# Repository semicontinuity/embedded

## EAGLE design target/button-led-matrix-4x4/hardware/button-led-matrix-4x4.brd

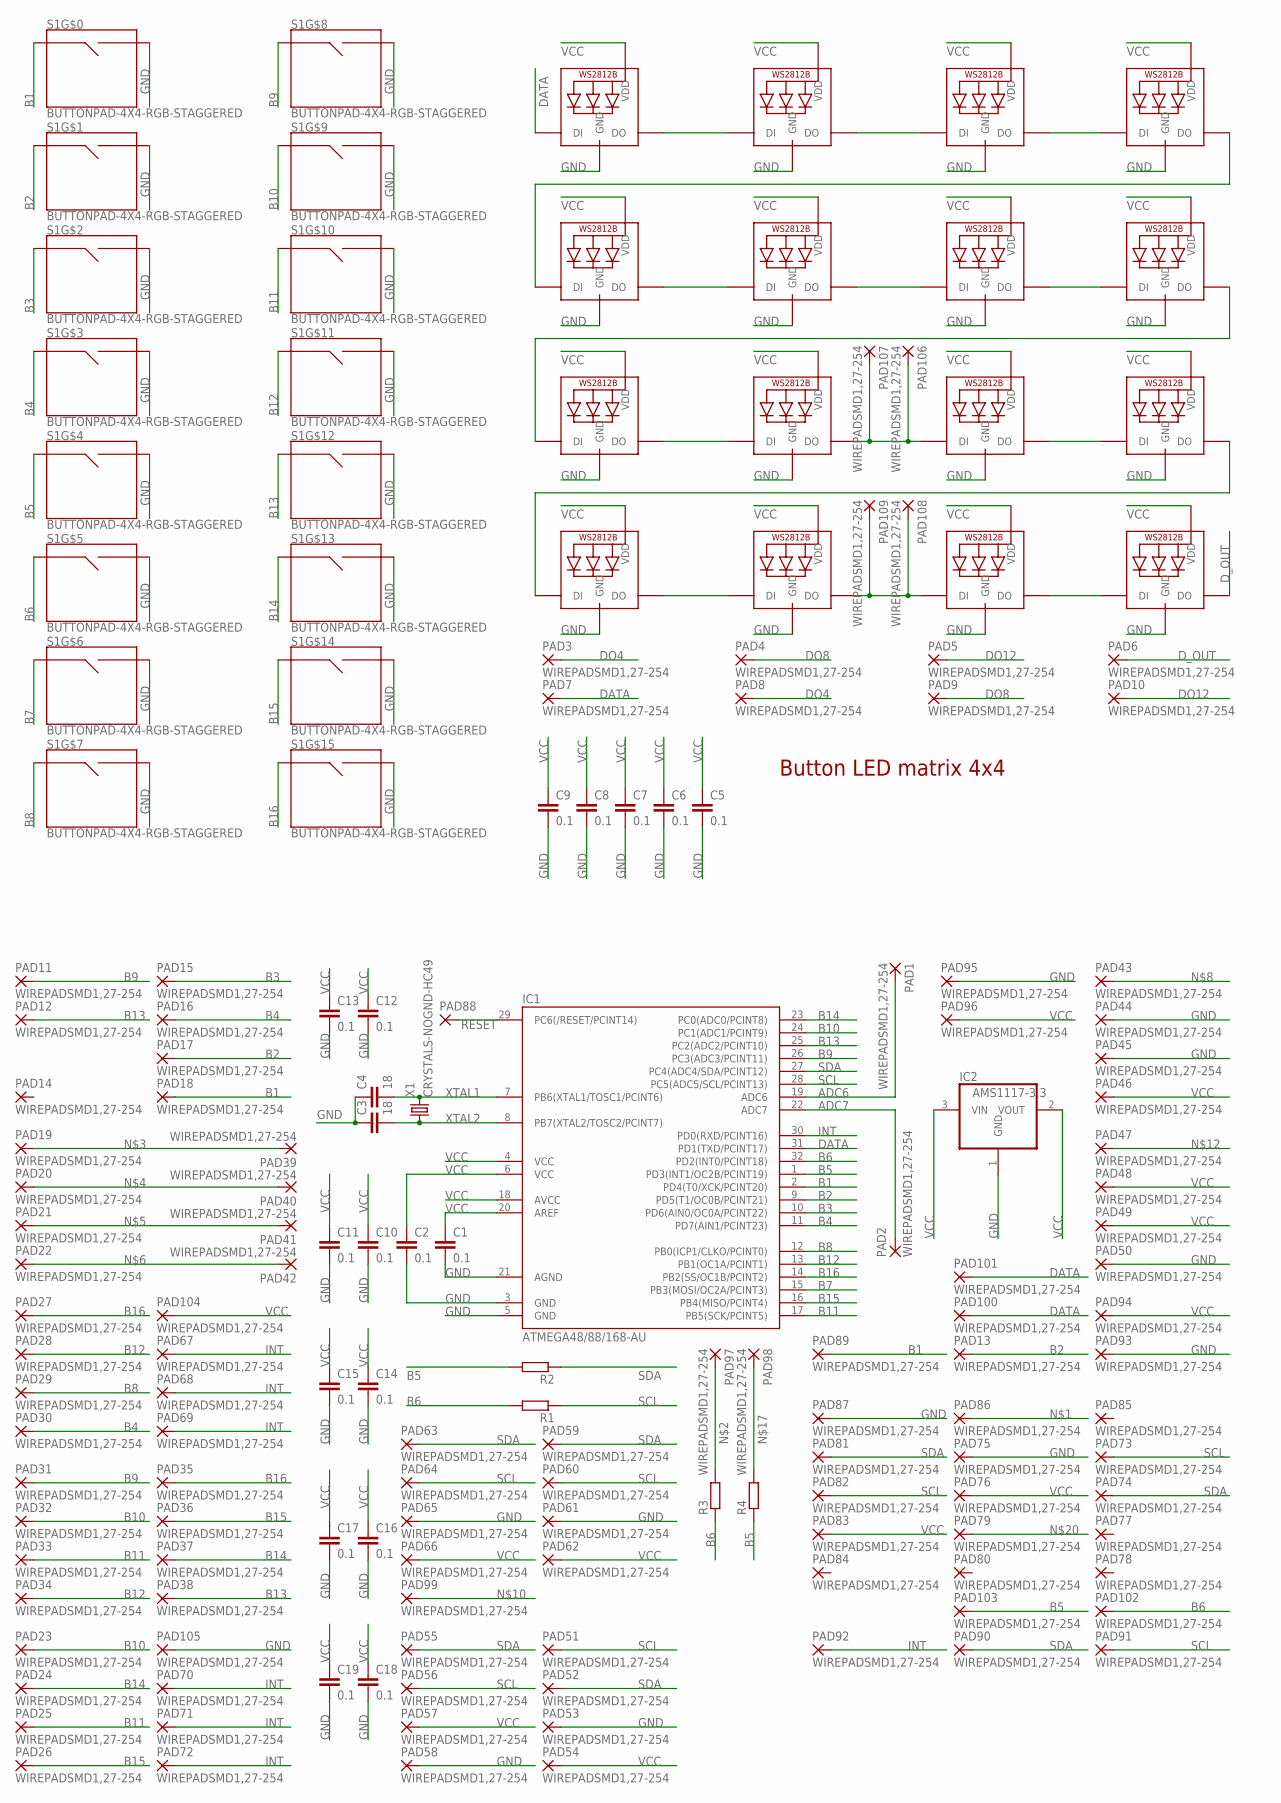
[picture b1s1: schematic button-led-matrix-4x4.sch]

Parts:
C1, C2, C5, C6, C7, C8, C9, C10, C11, C12, C13, C14, C15, C16, C17, C18, C19: 0.1; C0805
C3, C4: 18; C0805
IC1: ATMEGA48/88/168-AU; TQFP32-08
IC2: AMS1117-3.3; SOT223
LED1, LED2, LED3, LED4, LED5, LED6, LED7, LED8, LED9, LED10, LED11, LED12, LED13, LED14, LED15, LED16: WS2812B_5050N; WS2812B-NARROW
PAD1, PAD2, PAD3, PAD4, PAD5, PAD6, PAD7, PAD8, PAD9, PAD10, PAD11, PAD12, PAD13, PAD14, PAD15, PAD16, PAD17, PAD18, PAD19, PAD20, PAD21, PAD22, PAD23, PAD24, PAD25, PAD26, PAD27, PAD28, PAD29, PAD30, PAD31, PAD32, PAD33, PAD34, PAD35, PAD36, PAD37, PAD38, PAD39, PAD40, PAD41, PAD42, PAD43, PAD44, PAD45, PAD46, PAD47, PAD48, PAD49, PAD50, PAD51, PAD52, PAD53, PAD54, PAD55, PAD56, PAD57, PAD58, PAD59, PAD60, PAD61, PAD62, PAD63, PAD64, PAD65, PAD66, PAD67, PAD68, PAD69, PAD70, PAD71, PAD72, PAD73, PAD74, PAD75, PAD76, PAD77, PAD78, PAD79, PAD80, PAD81, PAD82, PAD83, PAD84, PAD85, PAD86, PAD87, PAD89, PAD90, PAD91, PAD92, PAD93, PAD94, PAD95, PAD96, PAD97, PAD98, PAD99, PAD100, PAD101, PAD102, PAD103, PAD104, PAD105, PAD106, PAD107, PAD108, PAD109: WIREPADSMD1,27-254; SMD1,27-2,54
PAD88: 1,6/0,8
R1, R2: R-EU_R1206; R1206
R3, R4: R-EU_R0805; R0805
S1: BUTTONPAD-4X4-RGB-STAGGERED; BUTTONPAD-4X4-STAGGERED
X1: CRYSTALS-NOGND-HC49; HC49

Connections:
ADC6: IC1.19 (ADC6), PAD1.1
ADC7: IC1.22 (ADC7), PAD2.1
B1: IC1.2 (PD4(T0/XCK/PCINT20)), PAD18.1, PAD89.1, S1.SIG0 (SIG1)
B2: IC1.9 (PD5(T1/OC0B/PCINT21)), PAD13.1, PAD17.1, S1.SIG2 (SIG1)
B3: IC1.10 (PD6(AIN0/OC0A/PCINT22)), PAD15.1, S1.SIG4 (SIG1)
B4: IC1.11 (PD7(AIN1/PCINT23)), PAD16.1, PAD30.1, S1.SIG6 (SIG1)
B5: IC1.1 (PD3(INT1/OC2B/PCINT19)), PAD103.1, R2.2, R4.1, S1.SIG8 (SIG1)
B6: IC1.32 (PD2(INT0/PCINT18)), PAD102.1, R1.2, R3.1, S1.SIG10 (SIG1)
B7: IC1.15 (PB3(MOSI/OC2A/PCINT3)), S1.SIG12 (SIG1)
B8: IC1.12 (PB0(ICP1/CLKO/PCINT0)), PAD29.1, S1.SIG14 (SIG1)
B9: IC1.26 (PC3(ADC3/PCINT11)), PAD11.1, PAD31.1, S1.SIG16 (SIG1)
B10: IC1.24 (PC1(ADC1/PCINT9)), PAD23.1, PAD32.1, S1.SIG18 (SIG1)
B11: IC1.17 (PB5(SCK/PCINT5)), PAD25.1, PAD33.1, S1.SIG20 (SIG1)
B12: IC1.13 (PB1(OC1A/PCINT1)), PAD28.1, PAD34.1, S1.SIG22 (SIG1)
B13: IC1.25 (PC2(ADC2/PCINT10)), PAD12.1, PAD38.1, S1.SIG24 (SIG1)
B14: IC1.23 (PC0(ADC0/PCINT8)), PAD24.1, PAD37.1, S1.SIG26 (SIG1)
B15: IC1.16 (PB4(MISO/PCINT4)), PAD26.1, PAD36.1, S1.SIG28 (SIG1)
B16: IC1.14 (PB2(SS/OC1B/PCINT2)), PAD27.1, PAD35.1, S1.SIG30 (SIG1)
DATA: IC1.31 (PD1(TXD/PCINT17)), LED1.4-DIN (DI), PAD7.1, PAD100.1, PAD101.1
DO1: LED1.2-DOUT (DO), LED2.4-DIN (DI)
DO2: LED2.2-DOUT (DO), LED3.4-DIN (DI)
DO3: LED3.2-DOUT (DO), LED4.4-DIN (DI)
DO4: LED4.2-DOUT (DO), LED5.4-DIN (DI), PAD3.1, PAD8.1
DO6: LED6.2-DOUT (DO), LED7.4-DIN (DI)
DO7: LED7.2-DOUT (DO), LED8.4-DIN (DI)
DO8: LED8.2-DOUT (DO), LED9.4-DIN (DI), PAD4.1, PAD9.1
DO9: LED9.2-DOUT (DO), LED10.4-DIN (DI)
DO10: LED10.2-DOUT (DO), LED11.4-DIN (DI), PAD106.1, PAD107.1
DO11: LED11.2-DOUT (DO), LED12.4-DIN (DI)
DO12: LED12.2-DOUT (DO), LED13.4-DIN (DI), PAD5.1, PAD10.1
DO13: LED13.2-DOUT (DO), LED14.4-DIN (DI)
DO14: LED14.2-DOUT (DO), LED15.4-DIN (DI), PAD108.1, PAD109.1
DO15: LED15.2-DOUT (DO), LED16.4-DIN (DI)
D_OUT: LED16.2-DOUT (DO), PAD6.1
FO5: LED5.2-DOUT (DO), LED6.4-DIN (DI)
GND: C1.2, C2.2, C3.1, C4.1, C5.2, C6.2, C7.2, C8.2, C9.2, C10.2, C11.2, C12.2, C13.2, C14.2, C15.2, C16.2, C17.2, C18.2, C19.2, IC1.3 (GND), IC1.5 (GND), IC1.21 (AGND), IC2.1 (GND), LED1.3-GND (GND), LED2.3-GND (GND), LED3.3-GND (GND), LED4.3-GND (GND), LED5.3-GND (GND), LED6.3-GND (GND), LED7.3-GND (GND), LED8.3-GND (GND), LED9.3-GND (GND), LED10.3-GND (GND), LED11.3-GND (GND), LED12.3-GND (GND), LED13.3-GND (GND), LED14.3-GND (GND), LED15.3-GND (GND), LED16.3-GND (GND), PAD44.1, PAD45.1, PAD50.1, PAD53.1, PAD58.1, PAD61.1, PAD65.1, PAD75.1, PAD87.1, PAD93.1, PAD95.1, PAD105.1, S1.SIG1 (SIG2), S1.SIG3 (SIG2), S1.SIG5 (SIG2), S1.SIG7 (SIG2), S1.SIG9 (SIG2), S1.SIG11 (SIG2), S1.SIG13 (SIG2), S1.SIG15 (SIG2), S1.SIG17 (SIG2), S1.SIG19 (SIG2), S1.SIG21 (SIG2), S1.SIG23 (SIG2), S1.SIG25 (SIG2), S1.SIG27 (SIG2), S1.SIG29 (SIG2), S1.SIG31 (SIG2)
INT: IC1.30 (PD0(RXD/PCINT16)), PAD67.1, PAD68.1, PAD69.1, PAD70.1, PAD71.1, PAD72.1, PAD92.1
unnamed: PAD97.1, R3.2
unnamed: PAD19.1, PAD39.1
unnamed: PAD20.1, PAD40.1
unnamed: PAD21.1, PAD41.1
unnamed: PAD22.1, PAD42.1
unnamed: PAD98.1, R4.2
RESET: IC1.29 (PC6(/RESET/PCINT14)), PAD88.1
SCL: IC1.28 (PC5(ADC5/SCL/PCINT13)), PAD51.1, PAD56.1, PAD60.1, PAD64.1, PAD73.1, PAD82.1, PAD91.1, R1.1
SDA: IC1.27 (PC4(ADC4/SDA/PCINT12)), PAD52.1, PAD55.1, PAD59.1, PAD63.1, PAD74.1, PAD81.1, PAD90.1, R2.1
VCC: C1.1, C2.1, C5.1, C6.1, C7.1, C8.1, C9.1, C10.1, C11.1, C12.1, C13.1, C14.1, C15.1, C16.1, C17.1, C18.1, C19.1, IC1.4 (VCC), IC1.6 (VCC), IC1.18 (AVCC), IC1.20 (AREF), IC2.2 (VOUT), IC2.3 (VIN), LED1.1-VDD (VDD), LED2.1-VDD (VDD), LED3.1-VDD (VDD), LED4.1-VDD (VDD), LED5.1-VDD (VDD), LED6.1-VDD (VDD), LED7.1-VDD (VDD), LED8.1-VDD (VDD), LED9.1-VDD (VDD), LED10.1-VDD (VDD), LED11.1-VDD (VDD), LED12.1-VDD (VDD), LED13.1-VDD (VDD), LED14.1-VDD (VDD), LED15.1-VDD (VDD), LED16.1-VDD (VDD), PAD46.1, PAD48.1, PAD49.1, PAD54.1, PAD57.1, PAD62.1, PAD66.1, PAD76.1, PAD83.1, PAD94.1, PAD96.1, PAD104.1
XTAL1: C4.2, IC1.7 (PB6(XTAL1/TOSC1/PCINT6)), X1.2
XTAL2: C3.2, IC1.8 (PB7(XTAL2/TOSC2/PCINT7)), X1.1

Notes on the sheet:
Button LED matrix 4x4

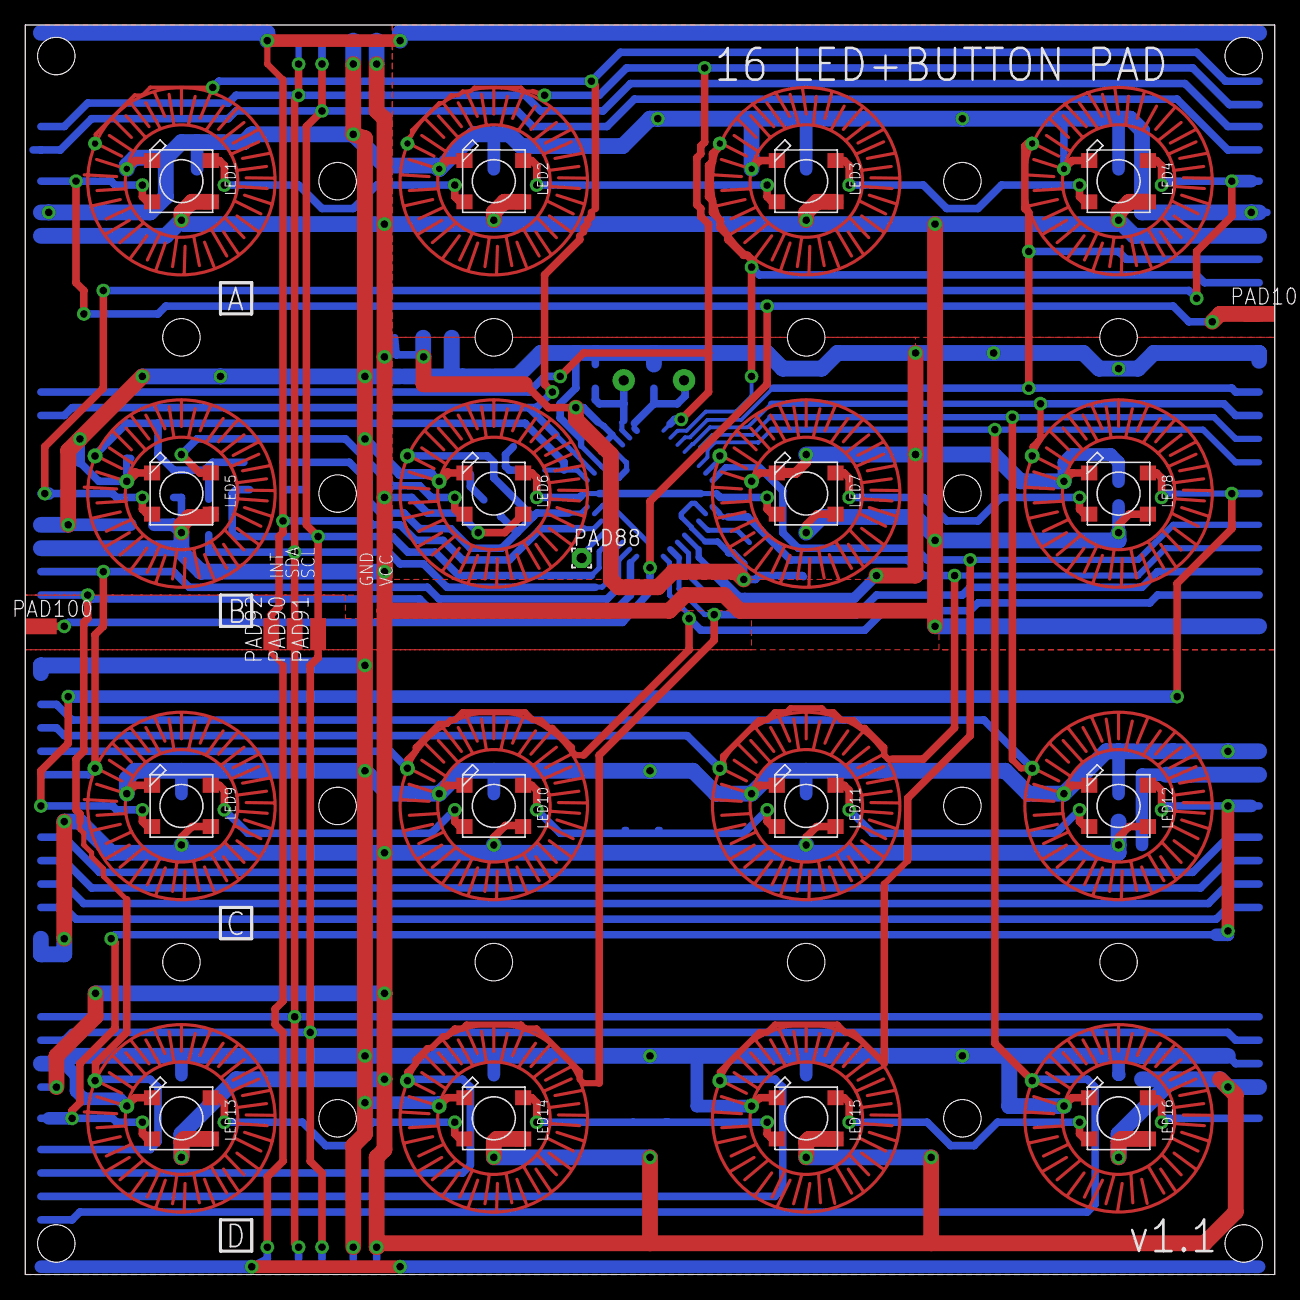
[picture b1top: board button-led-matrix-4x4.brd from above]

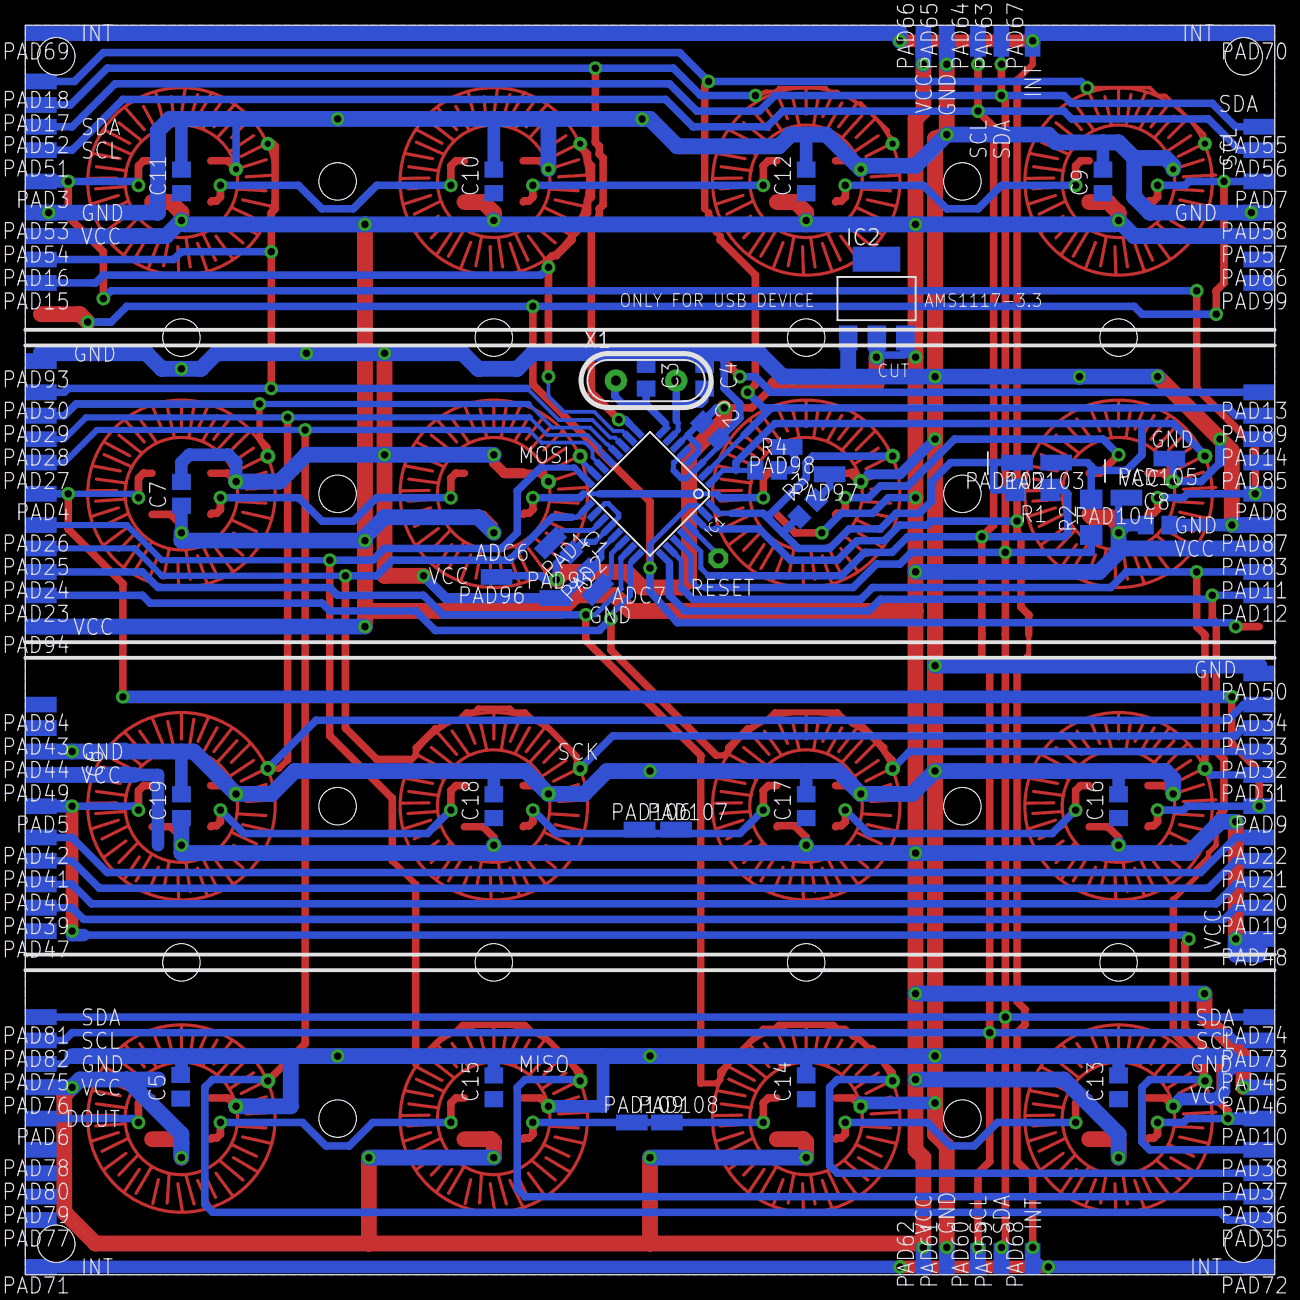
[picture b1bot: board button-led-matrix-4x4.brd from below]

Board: 2 copper layers, 100.0 x 100.0 mm, 152 parts (129 on the bottom side), 49 nets.

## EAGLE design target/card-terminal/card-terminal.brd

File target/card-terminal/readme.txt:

Card terminal

Device in development, featuring smartcard or SIM card slot, SPI interface, LCD display, keypad, serial and USB port.

Possible uses:

* CCID-compliant USB card terminal fith keypad and display
* USB HID device
* USB CDC device (USB-to-serial)
* Application host - providing resources to application running on a AVR card (Funcard)
* USB-to-SPI converter
* AVR programmer
* Generic development board

For serial connector, it is possible to use 6-pin or 4-pin FireWire connectors
(small size, hard to attach wrong cable, right number of pins,
crossed pairs in the cable - good for crossing RX/TX, RTS/CTS)

Revision A board is designed for AT90USB162 and SIM card slot.
Due to a small number of pins, peripherals are multiplexed and some glue logic is required.

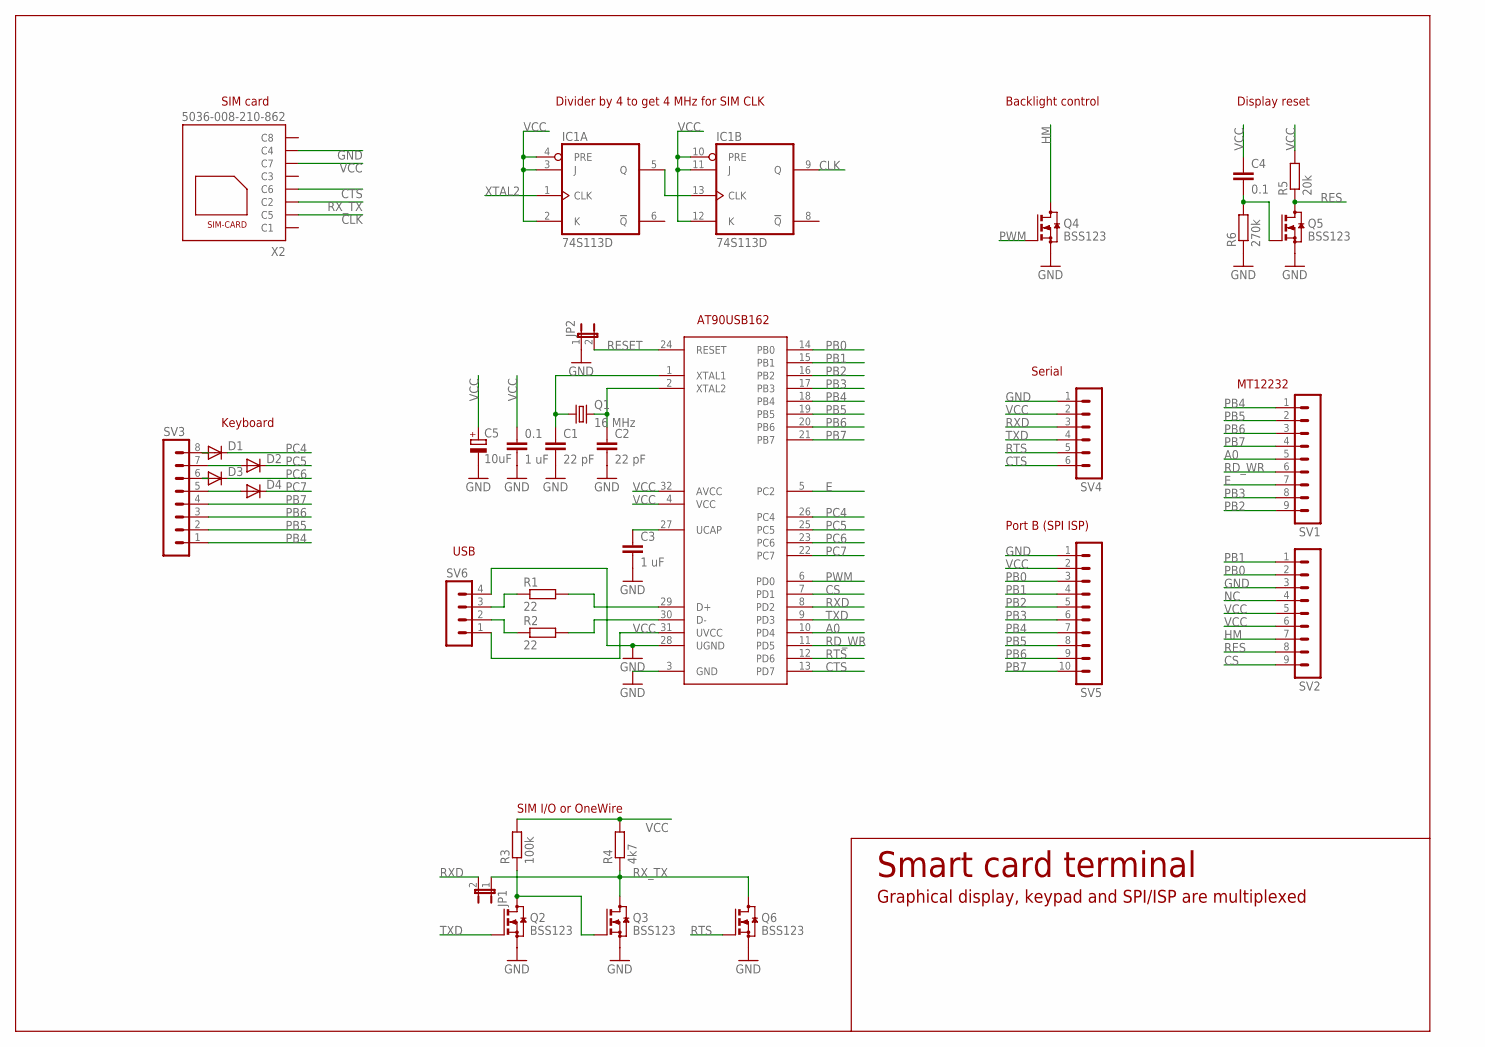
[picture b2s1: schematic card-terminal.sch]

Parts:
0.1: 1 uF; C0805
C1, C2: 22 pF; C0805
C3: 1 uF; C0805
C4: 0.1; C0805
C5: 10uF; 153CLV-0505
D1, D2, D3, D4: DIODE-MINIMELF; MINIMELF
IC1: 74S113D; SO14
JP1, JP2: JP1E; JP1
Q1: 16 MHz; HC49/S
Q2, Q3, Q4, Q5, Q6: BSS123; SOT23
R1, R2: 22; M0805
R3: 100k; M0805
R4: 4k7; M0805
R5: 20k; M0805
R6: 270k; M0805
SV1, SV2: MA09-1W
SV3: MA08-1
SV4: MA06-1
SV5: MA10-1W
SV6: MA04-1
U$1: AT90USB162; VQFP32
X2: 5036-008-210-862; 5036_008_210_862

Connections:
A0: SV1.5, U$1.10 (PD4)
CLK: IC1.9 (Q), X2.C5
CS: SV2.9, U$1.7 (PD1)
CTS: SV4.6, U$1.13 (PD7), X2.C6
E: SV1.7, U$1.5 (PC2)
F2: IC1.5 (Q), IC1.13 (CLK)
GND: 0.1.2, C1.2, C2.2, C3.2, C5.-, IC1.7 (GND), JP2.1, Q2.2 (S), Q3.2 (S), Q4.2 (S), Q5.2 (S), Q6.2 (S), R6.1, SV2.3, SV4.1, SV5.1, SV6.4, U$1.3 (GND), U$1.28 (UGND), X2.C4
HM: Q4.3 (D), SV2.7
unnamed: D1.A, SV3.8
unnamed: D2.A, SV3.7
unnamed: C4.2, Q5.1 (G), R6.2
unnamed: D3.A, SV3.6
unnamed: D4.A, SV3.5
unnamed: Q2.3 (D), Q3.1 (G), R3.1
unnamed: C3.1, U$1.27 (UCAP)
unnamed: R2.2, U$1.30 (D-)
unnamed: R1.2, U$1.29 (D+)
unnamed: R1.1, SV6.3
unnamed: R2.1, SV6.2
NC: SV2.4
PB0: SV2.2, SV5.3, U$1.14 (PB0)
PB1: SV2.1, SV5.4, U$1.15 (PB1)
PB2: SV1.9, SV5.5, U$1.16 (PB2)
PB3: SV1.8, SV5.6, U$1.17 (PB3)
PB4: SV1.1, SV3.1, SV5.7, U$1.18 (PB4)
PB5: SV1.2, SV3.2, SV5.8, U$1.19 (PB5)
PB6: SV1.3, SV3.3, SV5.9, U$1.20 (PB6)
PB7: SV1.4, SV3.4, SV5.10, U$1.21 (PB7)
PC4: D1.C, U$1.26 (PC4)
PC5: D2.C, U$1.25 (PC5)
PC6: D3.C, U$1.23 (PC6)
PC7: D4.C, U$1.22 (PC7)
PWM: Q4.1 (G), U$1.6 (PD0)
RD_WR: SV1.6, U$1.11 (PD5)
RES: Q5.3 (D), R5.1, SV2.8
RESET: JP2.2, U$1.24 (RESET)
RTS: Q6.1 (G), SV4.5, U$1.12 (PD6)
RXD: JP1.2, SV4.3, U$1.8 (PD2)
RX_TX: JP1.1, Q3.3 (D), Q6.3 (D), R4.1, X2.C2
TXD: Q2.1 (G), SV4.4, U$1.9 (PD3)
VCC: 0.1.1, C4.1, C5.+, IC1.2 (K), IC1.3 (J), IC1.4 (PRE), IC1.10 (PRE), IC1.11 (J), IC1.12 (K), IC1.14 (VCC), R3.2, R4.2, R5.2, SV2.5, SV2.6, SV4.2, SV5.2, SV6.1, U$1.4 (VCC), U$1.31 (UVCC), U$1.32 (AVCC), X2.C7
XTAL1: C1.1, Q1.1, U$1.1 (XTAL1)
XTAL2: C2.1, IC1.1 (CLK), Q1.2, U$1.2 (XTAL2)

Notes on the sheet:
Keyboard
SIM card
SIM I/O or OneWire
Backlight control
Display reset
USB
AT90USB162
Divider by 4 to get 4 MHz for SIM CLK
MT12232
Serial
Port B (SPI ISP)
Smart card terminal
Graphical display, keypad and SPI/ISP are multiplexed

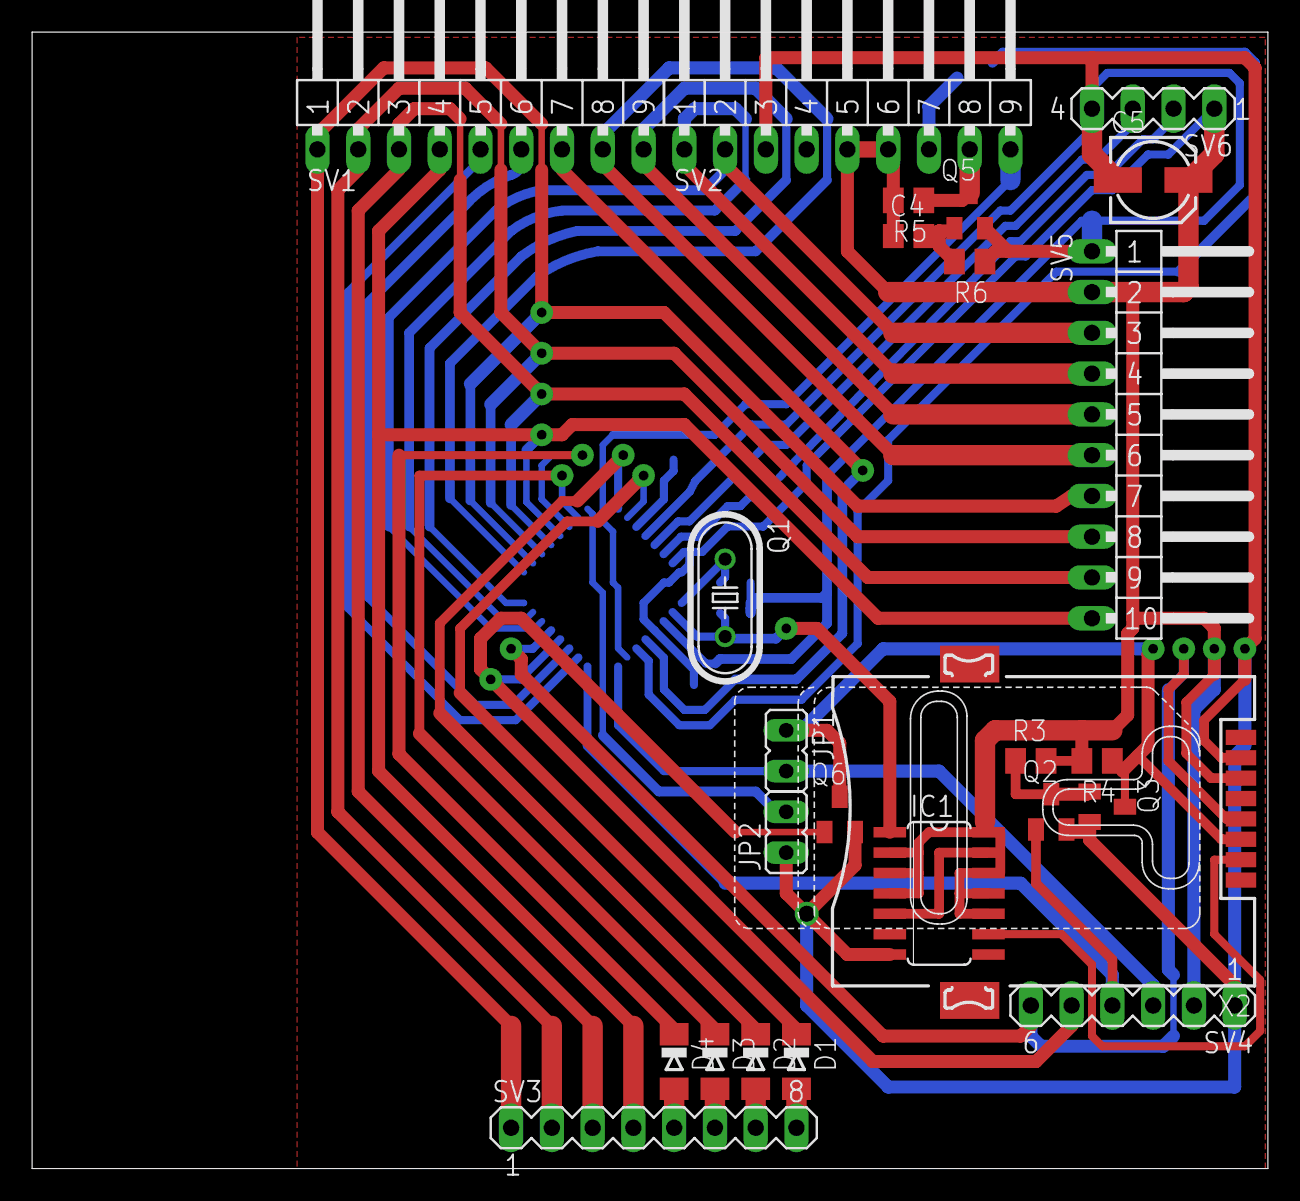
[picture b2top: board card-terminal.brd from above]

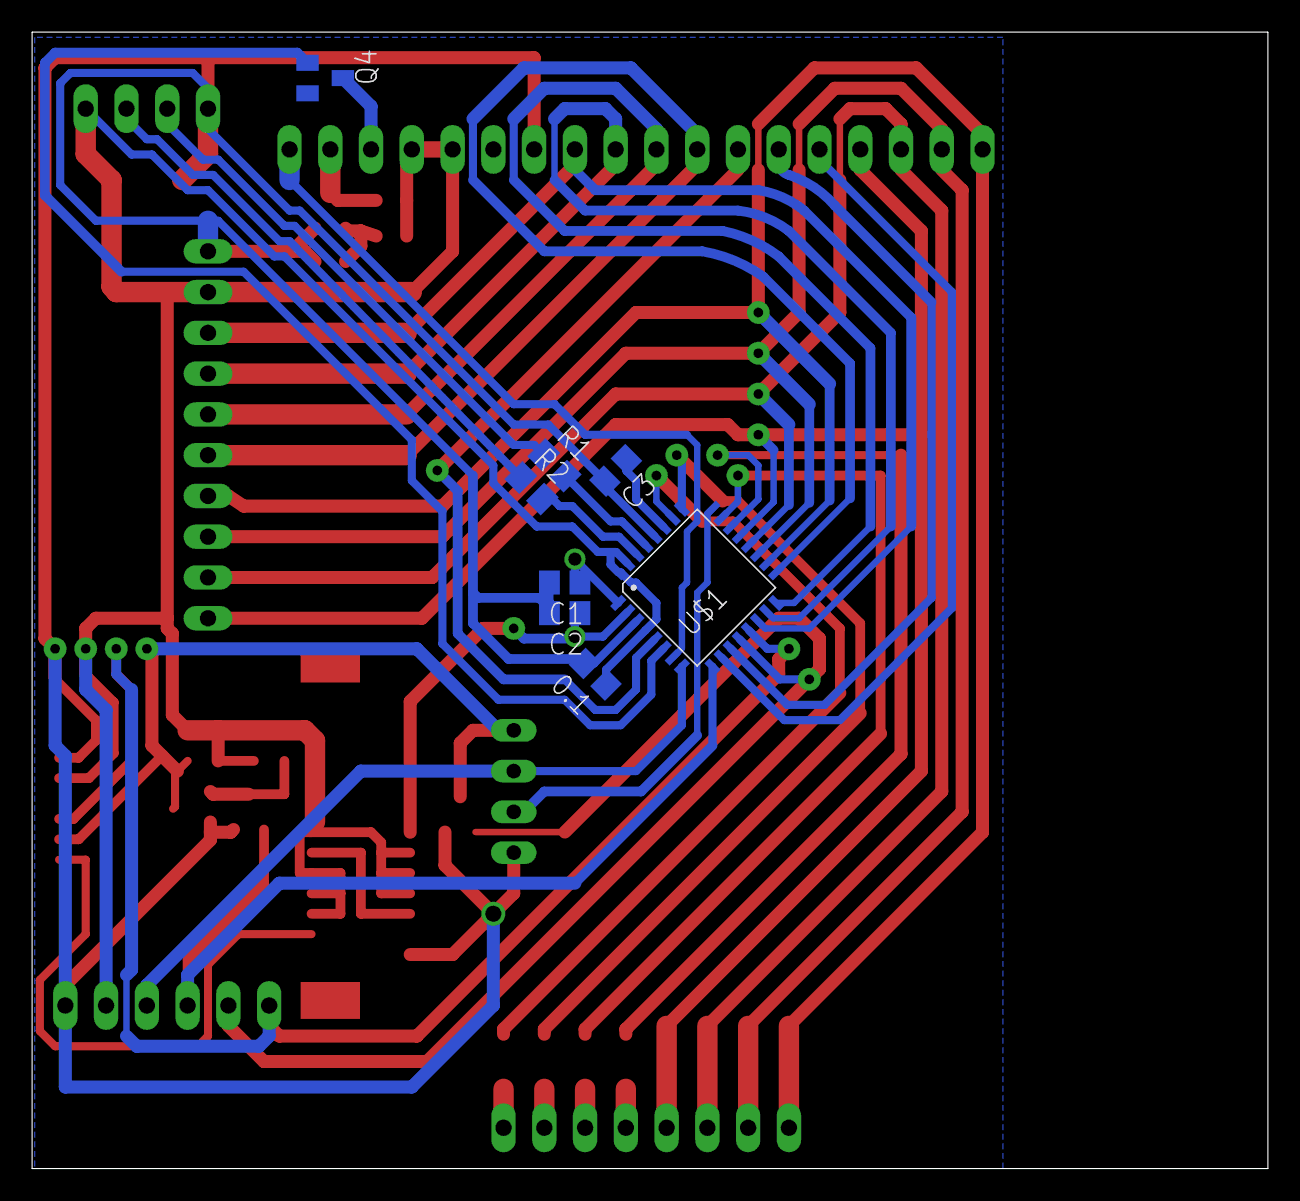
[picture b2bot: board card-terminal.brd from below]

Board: 2 copper layers, 77.0 x 70.8 mm, 33 parts (8 on the bottom side), 42 nets.

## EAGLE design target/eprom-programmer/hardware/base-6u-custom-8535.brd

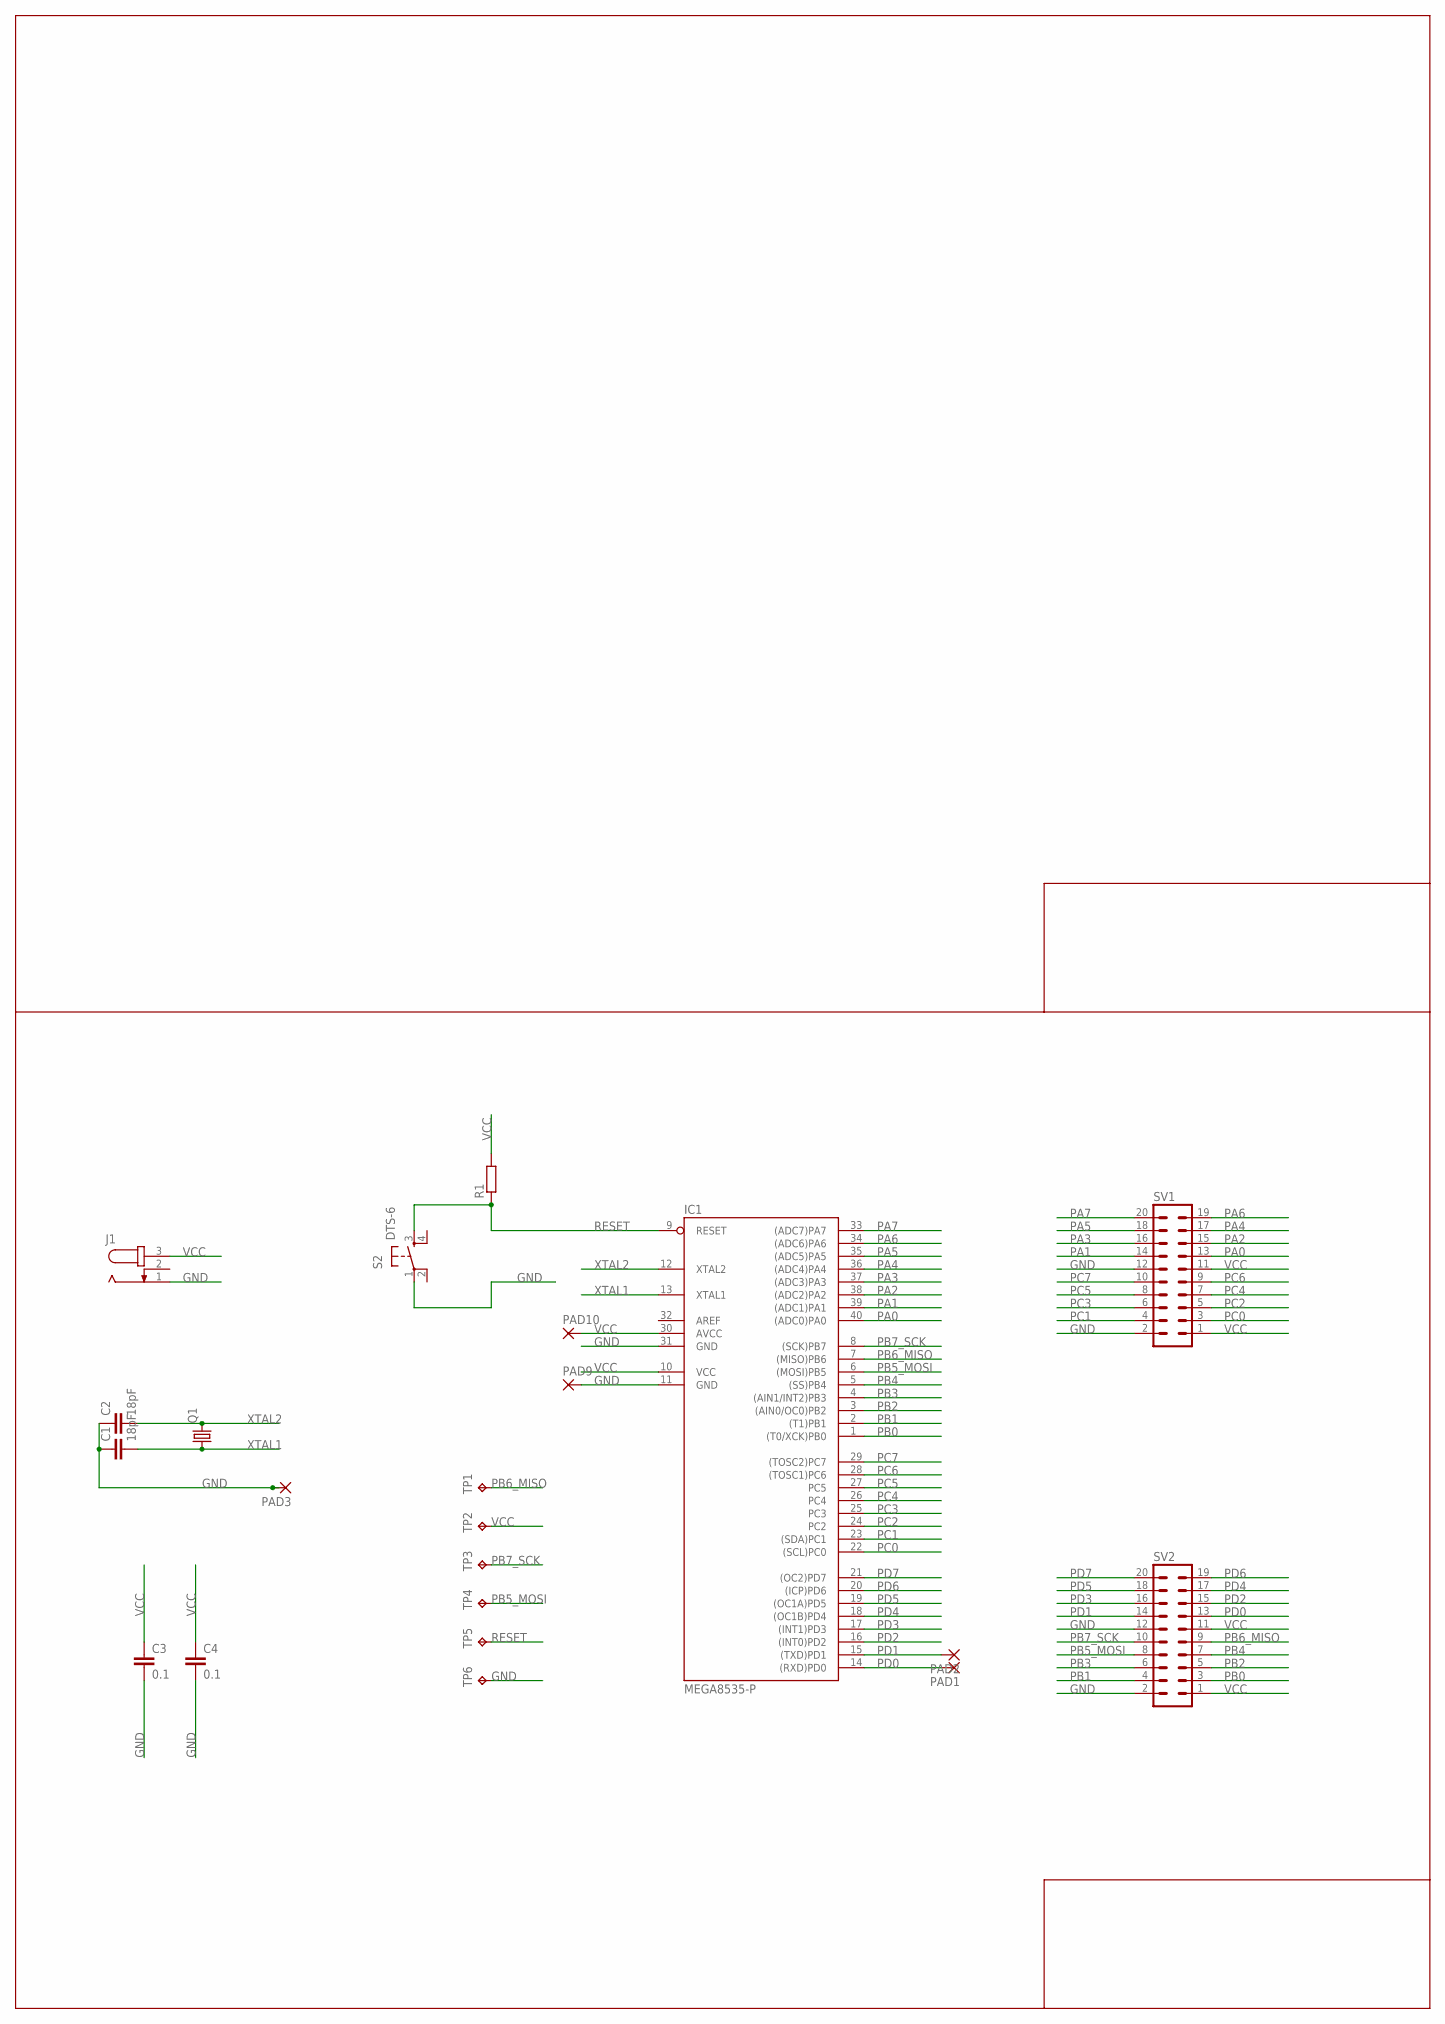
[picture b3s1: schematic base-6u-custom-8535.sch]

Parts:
C1, C2: 18pF; C0805
C3, C4: 0.1; C0805
IC1: MEGA8535-P; DIL40
J1: JACK-PLUG1; SPC4078
PAD1, PAD2, PAD3, PAD9, PAD10: 1,6/0,8
Q1: CRYSTALHC49S; HC49/S
R1: R-EU_0204/2V; 0204V
S2: DTS-6
SV1, SV2: MA10-2
TP1, TP2, TP3, TP4, TP5, TP6: TPTP16R; TP16R

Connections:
GND: C1.1, C2.1, C3.2, C4.2, IC1.11 (GND), IC1.31 (GND), J1.1, PAD3.1, PAD9.1, S2.1, SV1.2, SV1.12, SV2.2, SV2.12, TP6.TP
PA0: IC1.40 ((ADC0)PA0), SV1.13
PA1: IC1.39 ((ADC1)PA1), SV1.14
PA2: IC1.38 ((ADC2)PA2), SV1.15
PA3: IC1.37 ((ADC3)PA3), SV1.16
PA4: IC1.36 ((ADC4)PA4), SV1.17
PA5: IC1.35 ((ADC5)PA5), SV1.18
PA6: IC1.34 ((ADC6)PA6), SV1.19
PA7: IC1.33 ((ADC7)PA7), SV1.20
PB0: IC1.1 ((T0/XCK)PB0), SV2.3
PB1: IC1.2 ((T1)PB1), SV2.4
PB2: IC1.3 ((AIN0/OC0)PB2), SV2.5
PB3: IC1.4 ((AIN1/INT2)PB3), SV2.6
PB4: IC1.5 ((SS)PB4), SV2.7
PB5_MOSI: IC1.6 ((MOSI)PB5), SV2.8, TP4.TP
PB6_MISO: IC1.7 ((MISO)PB6), SV2.9, TP1.TP
PB7_SCK: IC1.8 ((SCK)PB7), SV2.10, TP3.TP
PC0: IC1.22 ((SCL)PC0), SV1.3
PC1: IC1.23 ((SDA)PC1), SV1.4
PC2: IC1.24 (PC2), SV1.5
PC3: IC1.25 (PC3), SV1.6
PC4: IC1.26 (PC4), SV1.7
PC5: IC1.27 (PC5), SV1.8
PC6: IC1.28 ((TOSC1)PC6), SV1.9
PC7: IC1.29 ((TOSC2)PC7), SV1.10
PD0: IC1.14 ((RXD)PD0), PAD1.1, SV2.13
PD1: IC1.15 ((TXD)PD1), PAD2.1, SV2.14
PD2: IC1.16 ((INT0)PD2), SV2.15
PD3: IC1.17 ((INT1)PD3), SV2.16
PD4: IC1.18 ((OC1B)PD4), SV2.17
PD5: IC1.19 ((OC1A)PD5), SV2.18
PD6: IC1.20 ((ICP)PD6), SV2.19
PD7: IC1.21 ((OC2)PD7), SV2.20
RESET: IC1.9 (RESET), R1.1, S2.3, TP5.TP
VCC: C3.1, C4.1, IC1.10 (VCC), IC1.30 (AVCC), J1.3, PAD10.1, R1.2, SV1.1, SV1.11, SV2.1, SV2.11, TP2.TP
XTAL1: C1.2, IC1.13 (XTAL1), Q1.1
XTAL2: C2.2, IC1.12 (XTAL2), Q1.2

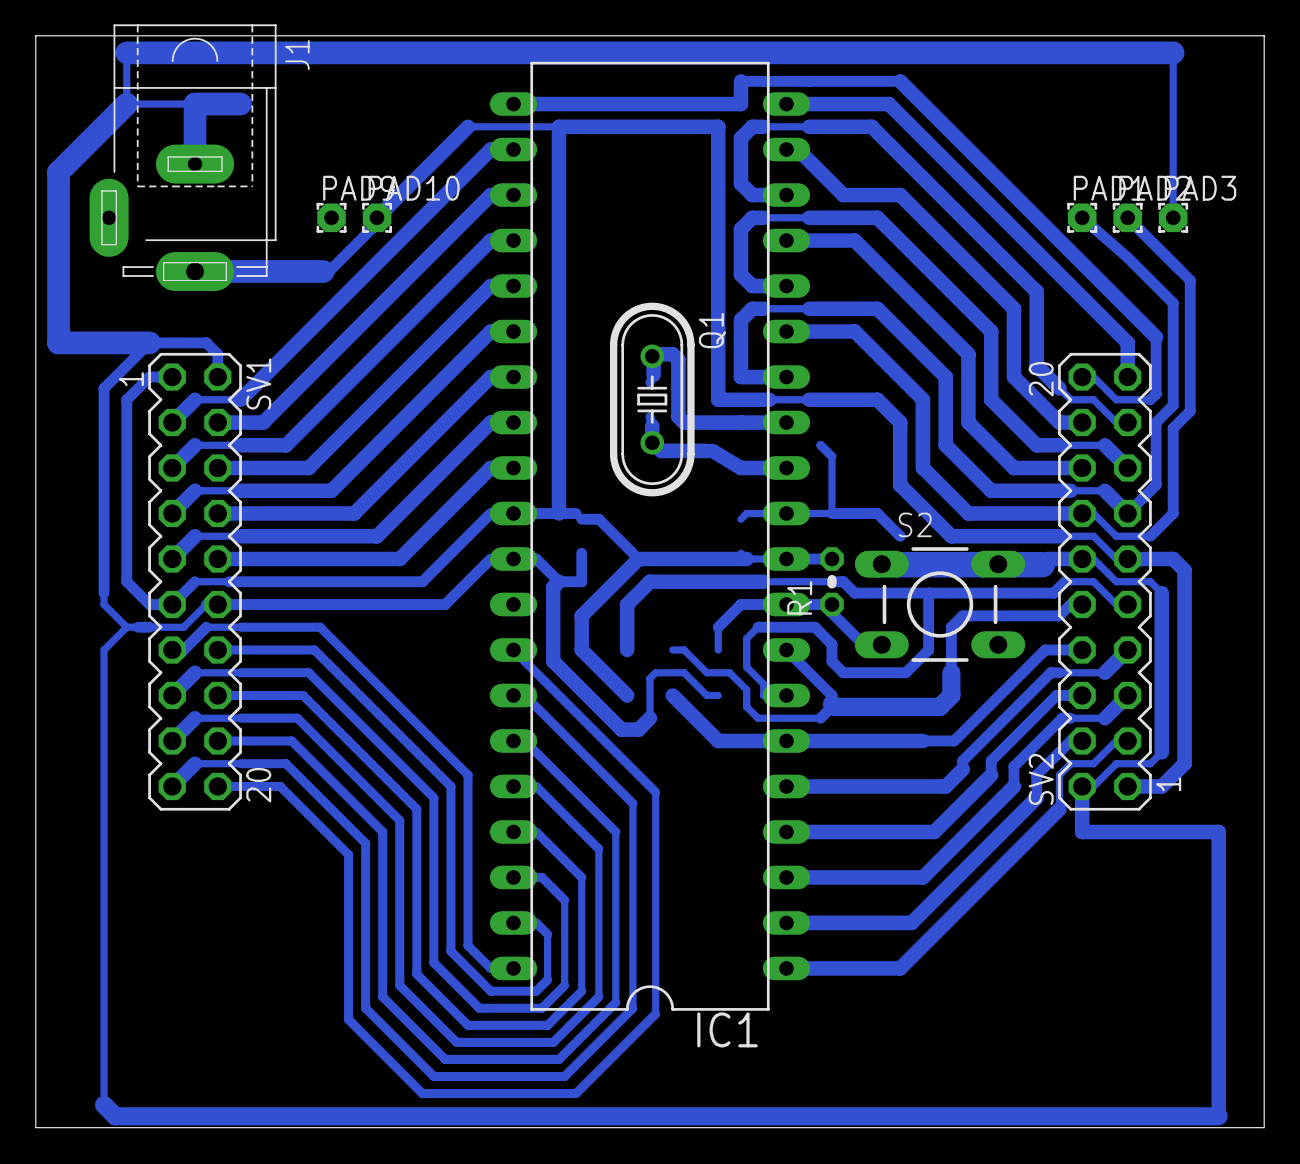
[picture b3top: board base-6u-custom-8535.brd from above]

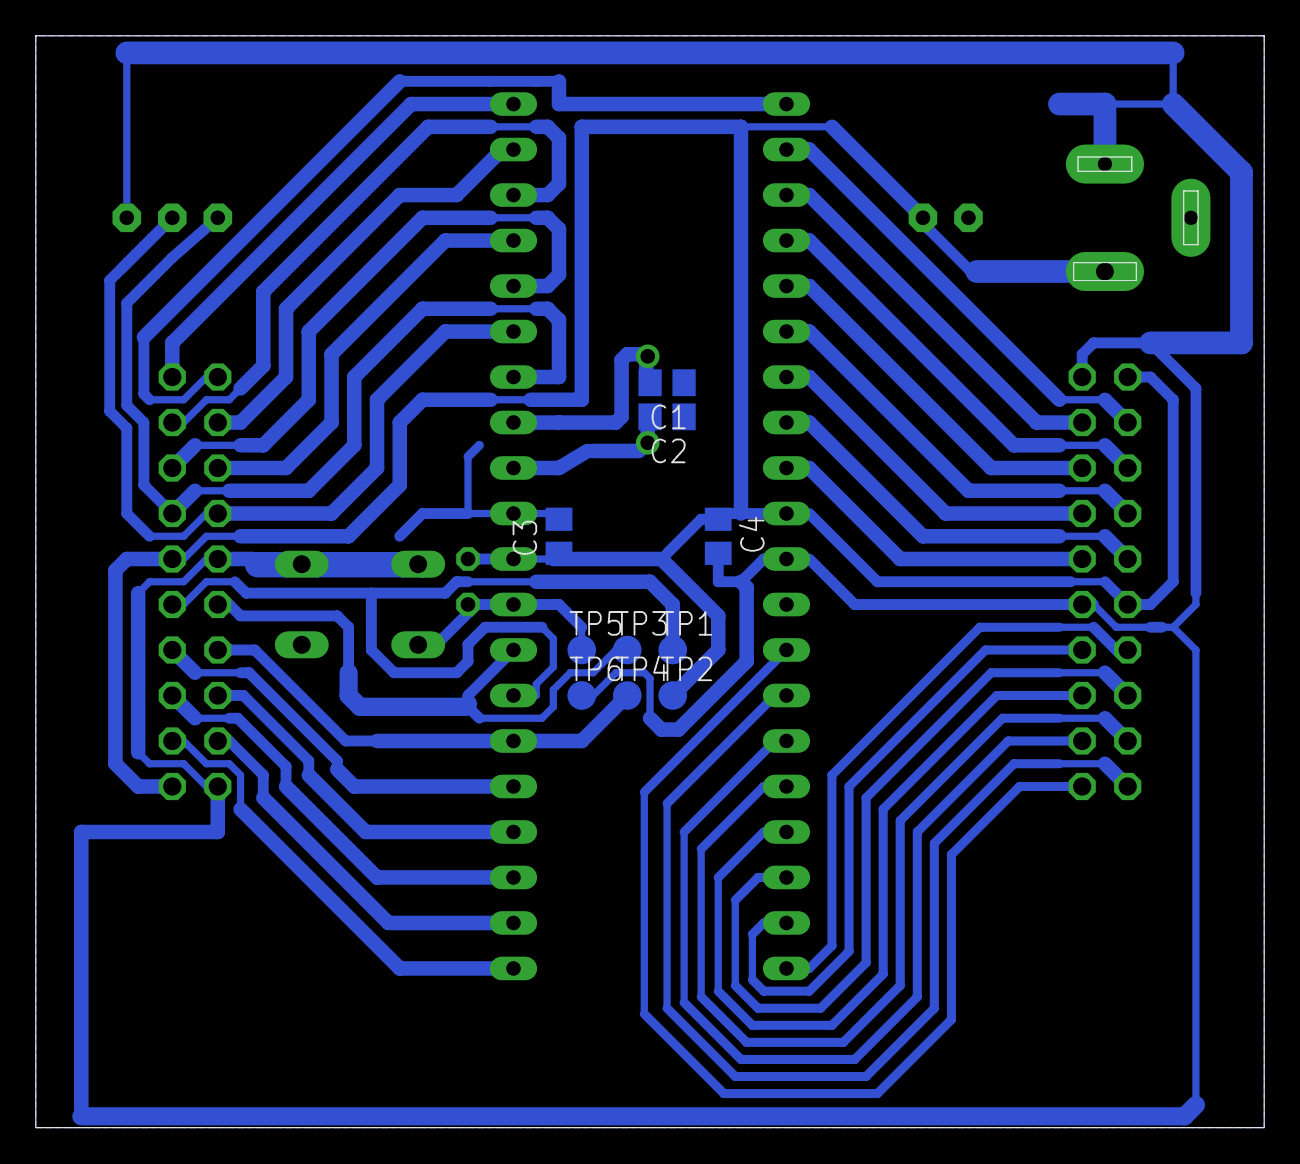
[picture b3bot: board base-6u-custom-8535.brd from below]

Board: 2 copper layers, 68.6 x 61.0 mm, 22 parts (10 on the bottom side), 37 nets.

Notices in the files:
parts and their libraries:
SparkFun-Switches: Licensing: Creative Commons ShareAlike 4.0 International - https://creativecommons.org/licenses/by-sa/4.0
